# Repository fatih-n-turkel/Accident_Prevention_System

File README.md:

# Accident_Prevention_System
Accident Prevention System like TESLA cars. (PCB + Code Design)

(https://www.youtube.com/watch?v=p_svqTvp0FE) As shown in the video, TESLA vehicles prevent accidents by autonomously moving to the most suitable place when they suddenly encounter obstacles. This system has been simulated in this project. It can be used in hobby electronic devices. For example, if the vehicle is driving on a straight road and suddenly detects an obstacle from the left side, it will pass to the right (right corner) if the right side is available. If not, it will move to the most available place, otherwise it will stop.

In the hardware design, I got help from the open source designs of SparkFun.

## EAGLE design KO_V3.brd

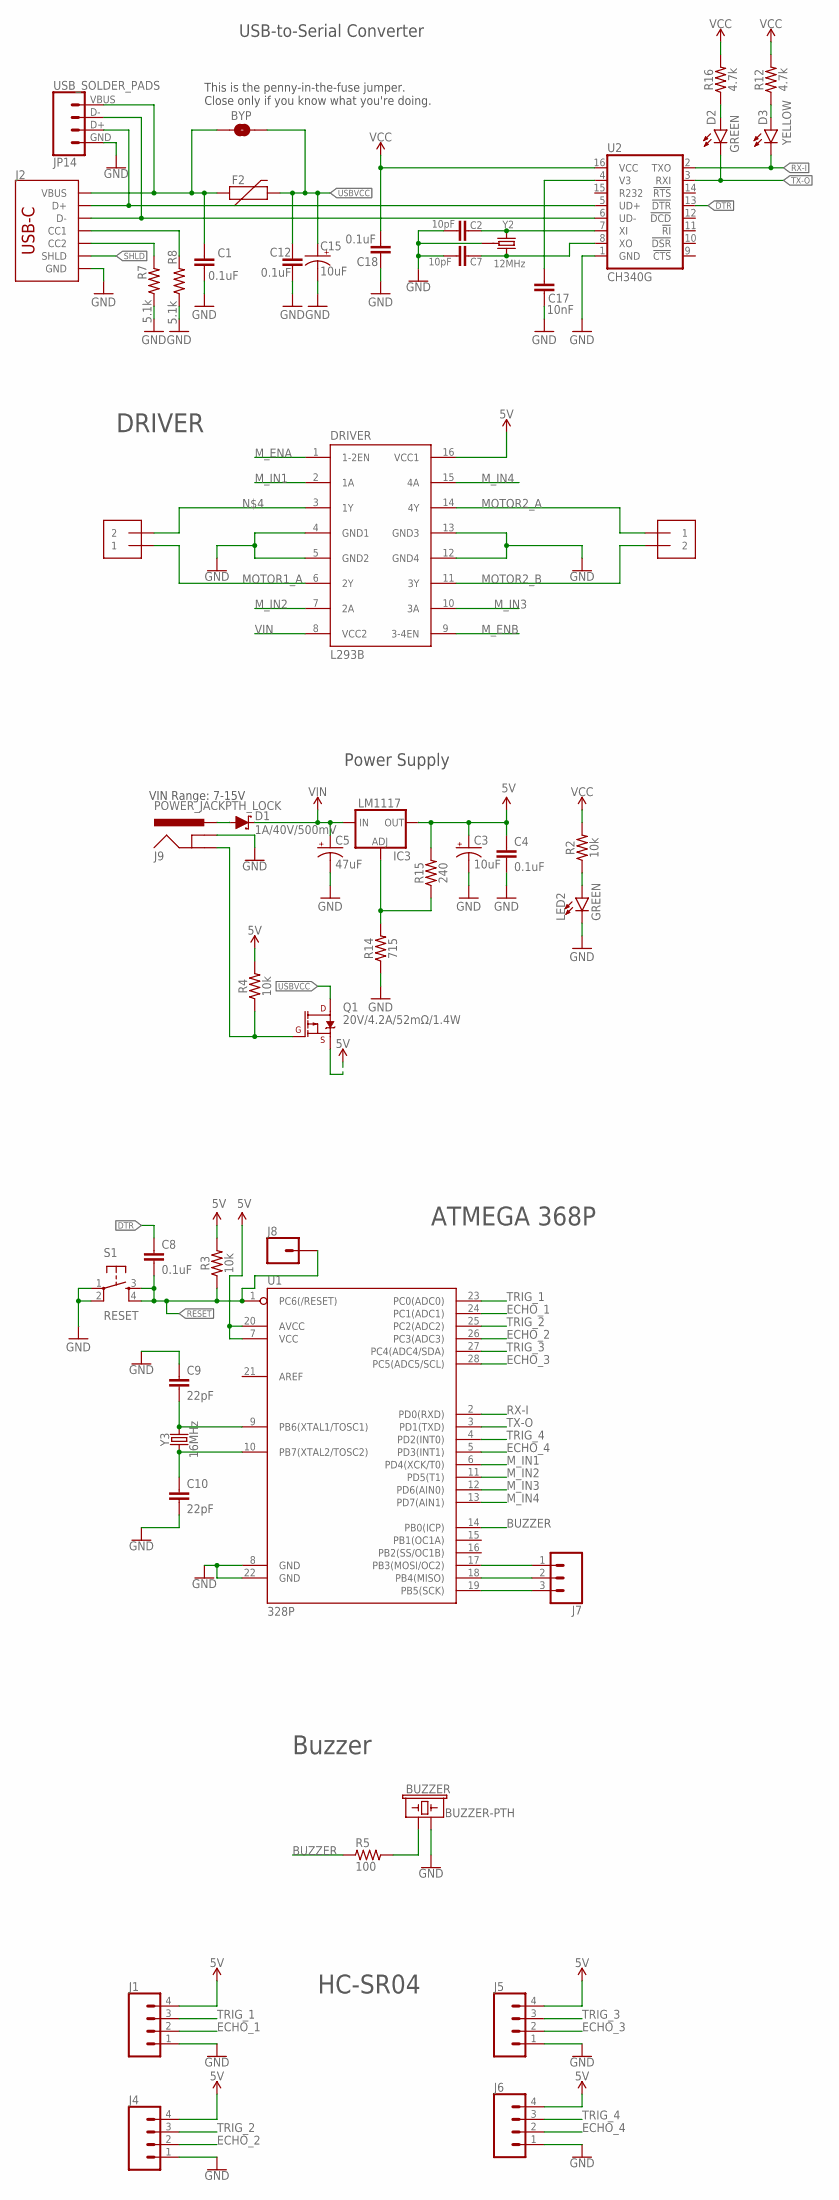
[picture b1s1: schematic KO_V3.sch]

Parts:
BUZZER: BUZZER-PTH; BUZZER-12MM
BYP: JUMPER-SMT_2_NO_SILK; SMT-JUMPER_2_NO_SILK
C1, C4, C8, C12, C18: 0.1uF; 0603
C2, C7: 10pF; 0603
C3, C15: 10uF; EIA3216
C5: 47uF; PANASONIC_D
C9, C10: 22pF; 0603
C17: 10nF; 0603
D1: 1A/40V/500mV; SMA-DIODE
D2: GREEN; LED-1206
D3: YELLOW; LED-1206-HIDDENSILK
DRIVER: L293B; DIL16
F2: 6V/2A; 1210
IC3: LM1117; SOT223
J1, J4, J5, J6: CONN_04; 1X04
J2: USB Female Type C Connector; USB-C-16P-2LAYER-PADS
J7: CONN_03LONGPADS; 1X03_LONGPADS
J8: CONN_01OFFSET; 1X01_OFFSET
J9: POWER_JACKPTH_LOCK; POWER_JACK_PTH_LOCK
JP14: USB_SOLDER_PADS; USB-SOLDER-PADS
LED2: GREEN; LED-1206
MOTOR_1, MOTOR_2: 1X2-3.5MM
Q1: 20V/4.2A/52mΩ/1.4W; SOT23-3
R2, R3, R4: 10k; 0603
R5: 100; RC-MASTER-SMD_R1206MP
R7, R8: 5.1k; 0603
R12, R16: 4.7k; 0603
R14: 715; 0603
R15: 240; 0603
S1: RESET; TACTILE-SWITCH-SMD
U1: 328P; DIP28
U2: CH340G; SO016
Y2: 12MHz; CRYSTAL-SMD-3.2X2.5MM
Y3: 16MHz; HC49US

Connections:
5V: C3.+, C4.1, DRIVER.16 (VCC1), IC3.2 (OUT), IC3.4 (OUT), J1.4, J4.4, J5.4, J6.4, Q1.2 (S), R3.2, R4.2, R15.2, U1.7 (VCC), U1.20 (AVCC)
!DTR!: U2.13 (!DTR)
BUZZER: R5.1, U1.14 (PB0(ICP))
CC1: J2.A5 (CC1), R8.2
CC2: J2.B5 (CC2), R7.2
D+: J2.A6 (D+), J2.B6 (D+), JP14.D+ (3), U2.5 (UD+)
D-: J2.A7 (D-), J2.B7 (D-), JP14.D- (2), U2.6 (UD-)
DTR: C8.1
ECHO_1: J1.2, U1.24 (PC1(ADC1))
ECHO_2: J4.2, U1.26 (PC3(ADC3))
ECHO_3: J5.2, U1.28 (PC5(ADC5/SCL))
ECHO_4: J6.2, U1.5 (PD3(INT1))
GND: BUZZER.- (2), C1.2, C2.2, C3.-, C4.2, C5.-, C7.2, C9.1, C10.2, C12.2, C15.-, C17.2, C18.2, DRIVER.4 (GND1), DRIVER.5 (GND2), DRIVER.12 (GND4), DRIVER.13 (GND3), J1.1, J2.GND, J2.GND2 (GND), J4.1, J5.1, J6.1, J9.GNDBREAK, JP14.GND (4), LED2.C, R7.1, R8.1, R14.1, S1.1, S1.2, U1.8 (GND), U1.22 (GND), U2.1 (GND), Y2.2 (GND), Y2.4 (GND)
INSERT: J9.GND, Q1.1 (G), R4.1
MOTOR1_A: DRIVER.6 (2Y), MOTOR_2.1
MOTOR2_A: DRIVER.14 (4Y), MOTOR_1.1
MOTOR2_B: DRIVER.11 (3Y), MOTOR_1.2
M_ENA: DRIVER.1 (1-2EN)
M_ENB: DRIVER.9 (3-4EN)
M_IN1: DRIVER.2 (1A), U1.6 (PD4(XCK/T0))
M_IN2: DRIVER.7 (2A), U1.11 (PD5(T1))
M_IN3: DRIVER.10 (3A), U1.12 (PD6(AIN0))
M_IN4: DRIVER.15 (4A), U1.13 (PD7(AIN1))
unnamed: C17.1, U2.4 (V3)
unnamed: C7.1, U2.8 (XO), Y2.3 (2)
unnamed: LED2.A, R2.1
unnamed: DRIVER.3 (1Y), MOTOR_2.2
unnamed: D2.A, R16.1
unnamed: BUZZER.+ (1), R5.2
unnamed: C2.1, U2.7 (XI), Y2.1
unnamed: D3.A, R12.1
unnamed: C9.2, U1.9 (PB6(XTAL1/TOSC1)), Y3.2
unnamed: C10.1, U1.10 (PB7(XTAL2/TOSC2)), Y3.1
unnamed: IC3.1 (ADJ), R14.2, R15.1
unnamed: J7.3, U1.19 (PB5(SCK))
unnamed: J7.2, U1.18 (PB4(MISO))
unnamed: J7.1, U1.17 (PB3(MOSI/OC2))
PWRIN: D1.A, J9.PWR
RESET: C8.2, J8.1, R3.1, S1.3, S1.4, U1.1 (PC6(/RESET))
RX-I: D3.C, U1.2 (PD0(RXD)), U2.2 (TXO)
SHLD: J2.SHLD1 (SHLD), J2.SHLD2 (SHLD), J2.SHLD3 (SHLD), J2.SHLD4 (SHLD)
TRIG_1: J1.3, U1.23 (PC0(ADC0))
TRIG_2: J4.3, U1.25 (PC2(ADC2))
TRIG_3: J5.3, U1.27 (PC4(ADC4/SDA))
TRIG_4: J6.3, U1.4 (PD2(INT0))
TX-O: D2.C, U1.3 (PD1(TXD)), U2.3 (RXI)
USBVCC: BYP.2, C12.1, C15.+, F2.2, Q1.3 (D)
VCC: C18.1, R2.2, R12.2, R16.2, U2.16 (VCC)
VIN: C5.+, D1.C, DRIVER.8 (VCC2), IC3.3 (IN)
VUSB: BYP.1, C1.1, F2.1, J2.VBUS1 (VBUS), J2.VBUS2 (VBUS), JP14.VBUS (1)

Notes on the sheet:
DRIVER
HC-SR04
Buzzer
ATMEGA 368P
USB-to-Serial Converter
This is the penny-in-the-fuse jumper. Close only if you know what you're doing.
Power Supply
VIN Range: 7-15V

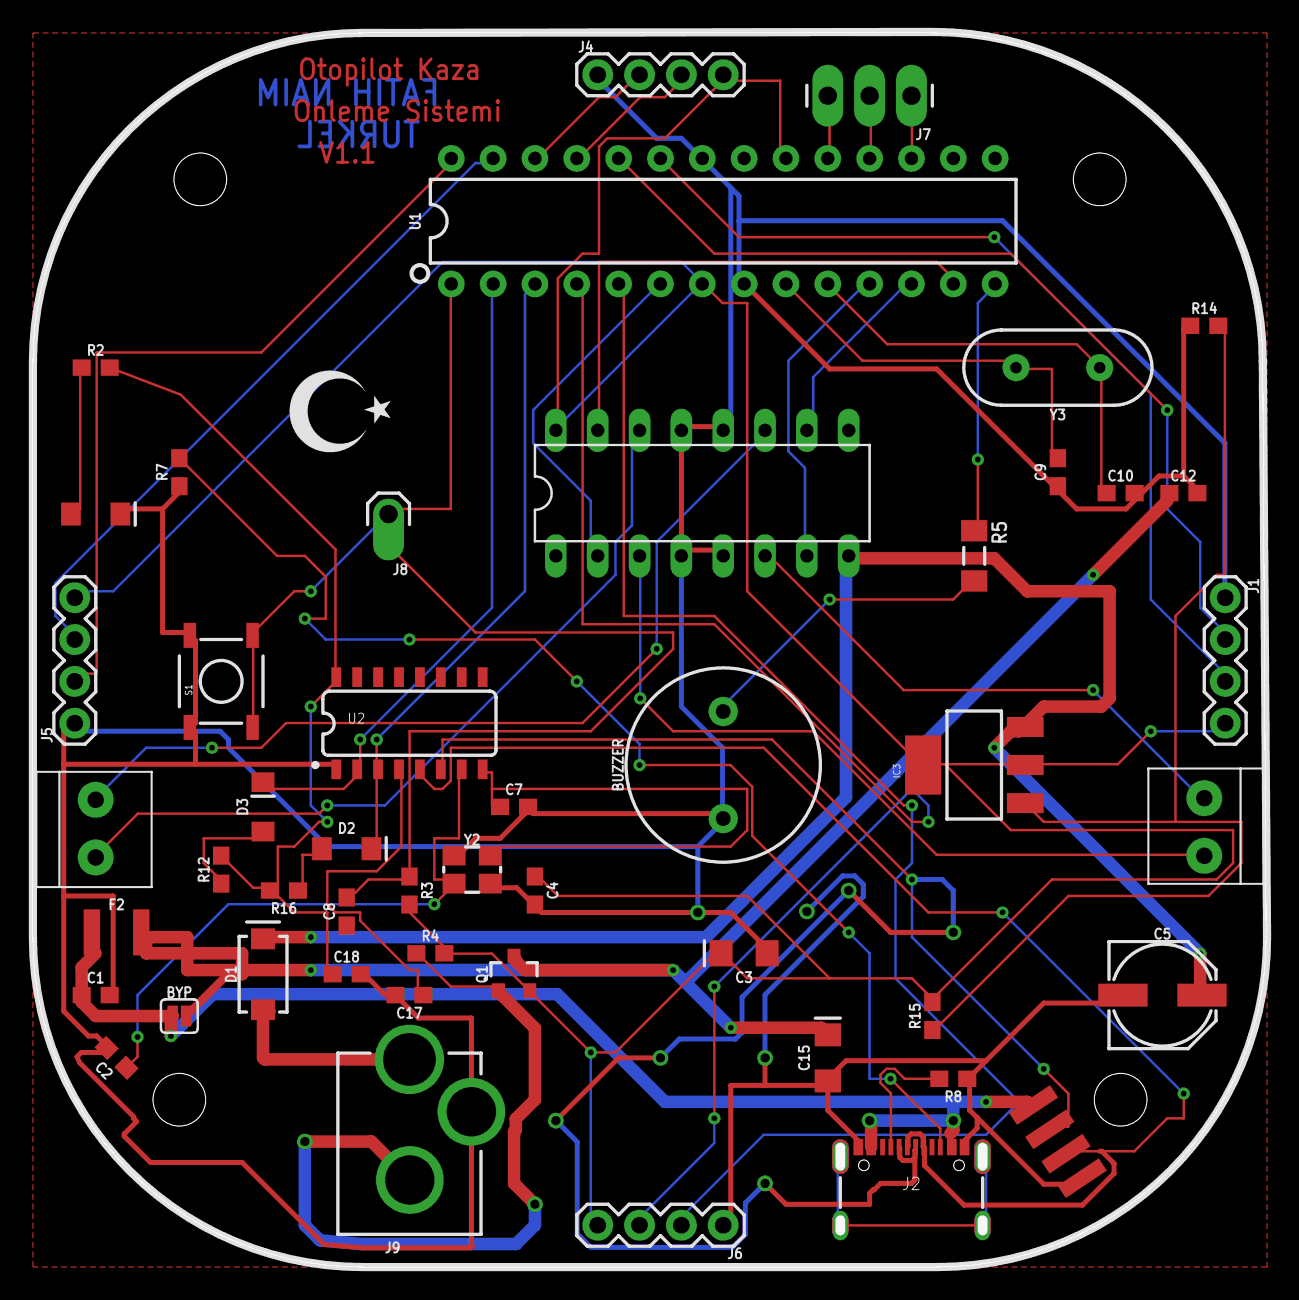
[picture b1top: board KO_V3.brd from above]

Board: 2 copper layers, 74.3 x 74.3 mm, 51 parts (1 on the bottom side), 46 nets.

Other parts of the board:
U$2, U$4: TR_MINI

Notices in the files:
parts and their libraries:
SparkFun-Connectors: Licensing: Creative Commons ShareAlike 4.0 International - https://creativecommons.org/licenses/by-sa/4.0
SparkFun-Resistors: Licensing: CC v3.0 Share-Alike You are welcome to use this library for commercial purposes.
